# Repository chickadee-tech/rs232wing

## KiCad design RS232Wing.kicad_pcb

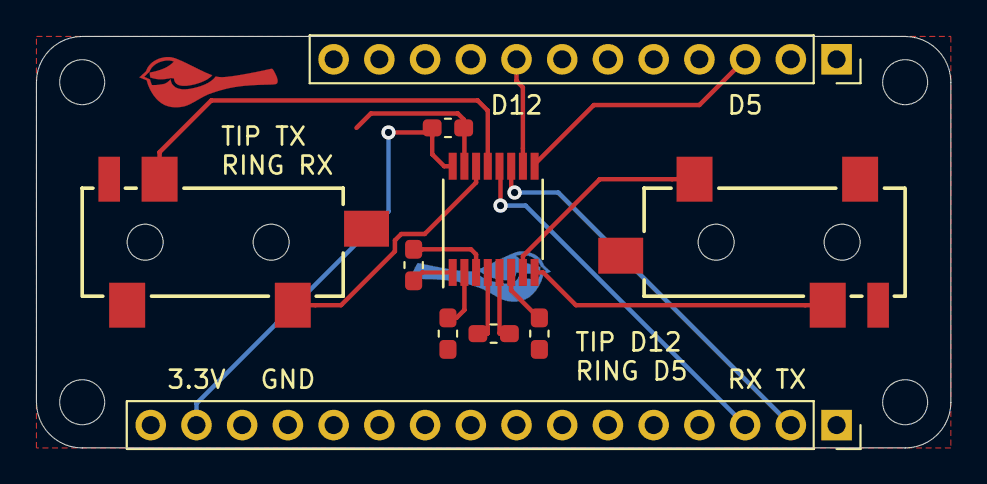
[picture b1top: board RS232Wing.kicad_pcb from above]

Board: 2 copper layers, 50.8 x 22.9 mm, 10 parts (0 on the bottom side), 16 nets.

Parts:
C1, C2, C3, C4, C5: 0.1uF; C_0603_1608Metric_Pad1.05x0.95mm_HandSolder
J1: Conn_01x16_Female; PinSocket_1x16_P2.54mm_Vertical
J2, J3: AudioJack3_SwitchTR; 4UCONN_19269_TRS
J4: Conn_01x12_Female; PinSocket_1x12_P2.54mm_Vertical
U1: MAX232; TSSOP-16_4.4x5mm_P0.65mm

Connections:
+3V3: C2.1, J1.15, U1.16
/D5: J4.3, U1.9
/D12: J4.8, U1.10
/R1: J2.R, U1.13
/R2: J3.R, U1.8
/RX: J1.3, U1.12
/T1: J2.T, U1.14
/T2: J3.T, U1.7
/TX: J1.2, U1.11
GND: C2.2, C4.2, C5.1, J1.13, J2.S, J3.S, U1.15
unnamed: C1.1, U1.1
unnamed: C1.2, U1.3
unnamed: C3.1, U1.4
unnamed: C3.2, U1.5
unnamed: C4.1, U1.2
unnamed: C5.2, U1.6
